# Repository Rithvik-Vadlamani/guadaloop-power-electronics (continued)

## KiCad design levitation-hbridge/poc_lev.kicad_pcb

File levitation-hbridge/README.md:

# poc_lev — levitation-coil H-bridge

KiCad 10 project for one nominal 60 V, bidirectional coil-driver channel. Built from the supplied brief, with the user's approved Bourns Kelvin pickup and revised component bands. No purchases or paid external services were used.

**Engineering review package. Hardware has not been built or powered.** The 30 A target, transient envelope and <5 nH commutation-loop target are not qualified. See the open release items in [DESIGN_NOTES.md](DESIGN_NOTES.md), especially the unknown charged-pack voltage, unmeasured coil, INA240 transient limit, heatsinks and requested human driver-pinout signoff.

The follow-up [hardware qualification review](HARDWARE_QUALIFICATION.md) includes conditional transient, ripple and thermal calculations. The user confirmed that no assembled board exists; physical qualification is blocked until hardware is available.

The approved [J3 edge-placement revision](INTERFACE_REVIEW.md) is applied: the header, control buffer, input resistors and auxiliary rail-entry components are regrouped near the bottom edge.

## Open and review

Open `poc_lev.kicad_pro` with KiCad 10.0.3 or later. The schematic is one flat sheet; the PCB is a routed four-layer, 146 × 96 mm board. Standard KiCad symbol/footprint libraries are required. Project-specific libraries are included and use `${KIPRJMOD}` paths.

- `poc_lev.kicad_sch` — editable schematic; exact 34-net specification.
- `poc_lev.kicad_pcb` — editable board, filled copper and four mounting holes.
- `poc_lev.kicad_pro`, `poc_lev.kicad_dru` — project settings and layout rules.
- `poc_lev.kicad_sym`, `lib.pretty/`, library tables — local symbols and footprints.
- `BOM.csv` — 64 electrical parts plus six test points and four mounting holes, including required component ratings.
- `VERIFICATION.md`, `reports/verification.json` — measured results and method.
- `DESIGN_NOTES.md` — source corrections, calculations, stackup and release items.
- `BRING_UP.md` — control pinout, current sign, logic states and required bench-test ladder.
- `reports/schematic-preview.png`, `reports/pcb-preview.png` — review images; native files remain authoritative.
- `sources/` — supplied brief and source documents/figures used during the review.

No fabrication order has been placed. No Gerber set is represented as approved for fabrication.

## Validation

On this Mac, run `zsh scripts/check.sh`. This invokes native KiCad ERC, native DRC and an independent parser that reconstructs schematic connectivity from wire/pin/label geometry, cross-checks the native XML netlist and checks the PCB pad mappings. Gate-loop measurements include component pad spans and the explicit source-return traces; via traversal contributes the nominal 1.6 mm board thickness. Parallel copper-plane returns are not assigned an invented length or inductance.

The matching requirement is checked within each half-bridge. The two shunt-to-filter copper paths are explicitly length matched. Decoupling distances are pad-center placement measurements; they are not field-extracted inductance values. Native DRC enforces 0.25 mm courtyard clearance and prohibits inner-layer tracks.

## Rebuild sources

The native files are ready to open without Python. Scripts are also supplied for reproducibility. `scripts/rebuild.sh` **overwrites the generated schematic and PCB**, so save any manual edits elsewhere first and close KiCad.

The build uses free, local software: KiCad 10.0.3, its bundled Python 3.9/pcbnew/wx, and NumPy, SciPy and Shapely in `.venv`. The virtual environment itself is not part of the delivery archive. On the build machine it was created with:

```sh
/Applications/KiCad/KiCad.app/Contents/Frameworks/Python.framework/Versions/3.9/bin/python3 -m venv .venv
.venv/bin/python -m pip install -r scripts/requirements.txt
zsh scripts/rebuild.sh
```

`KICAD_CLI`, `KICAD_PYTHON` and `KICAD_SITE_PACKAGES` can override the macOS tool locations. The source scripts also contain the installed standard-library location; adapt it if building on another operating system. No cloud autorouter or account is needed.

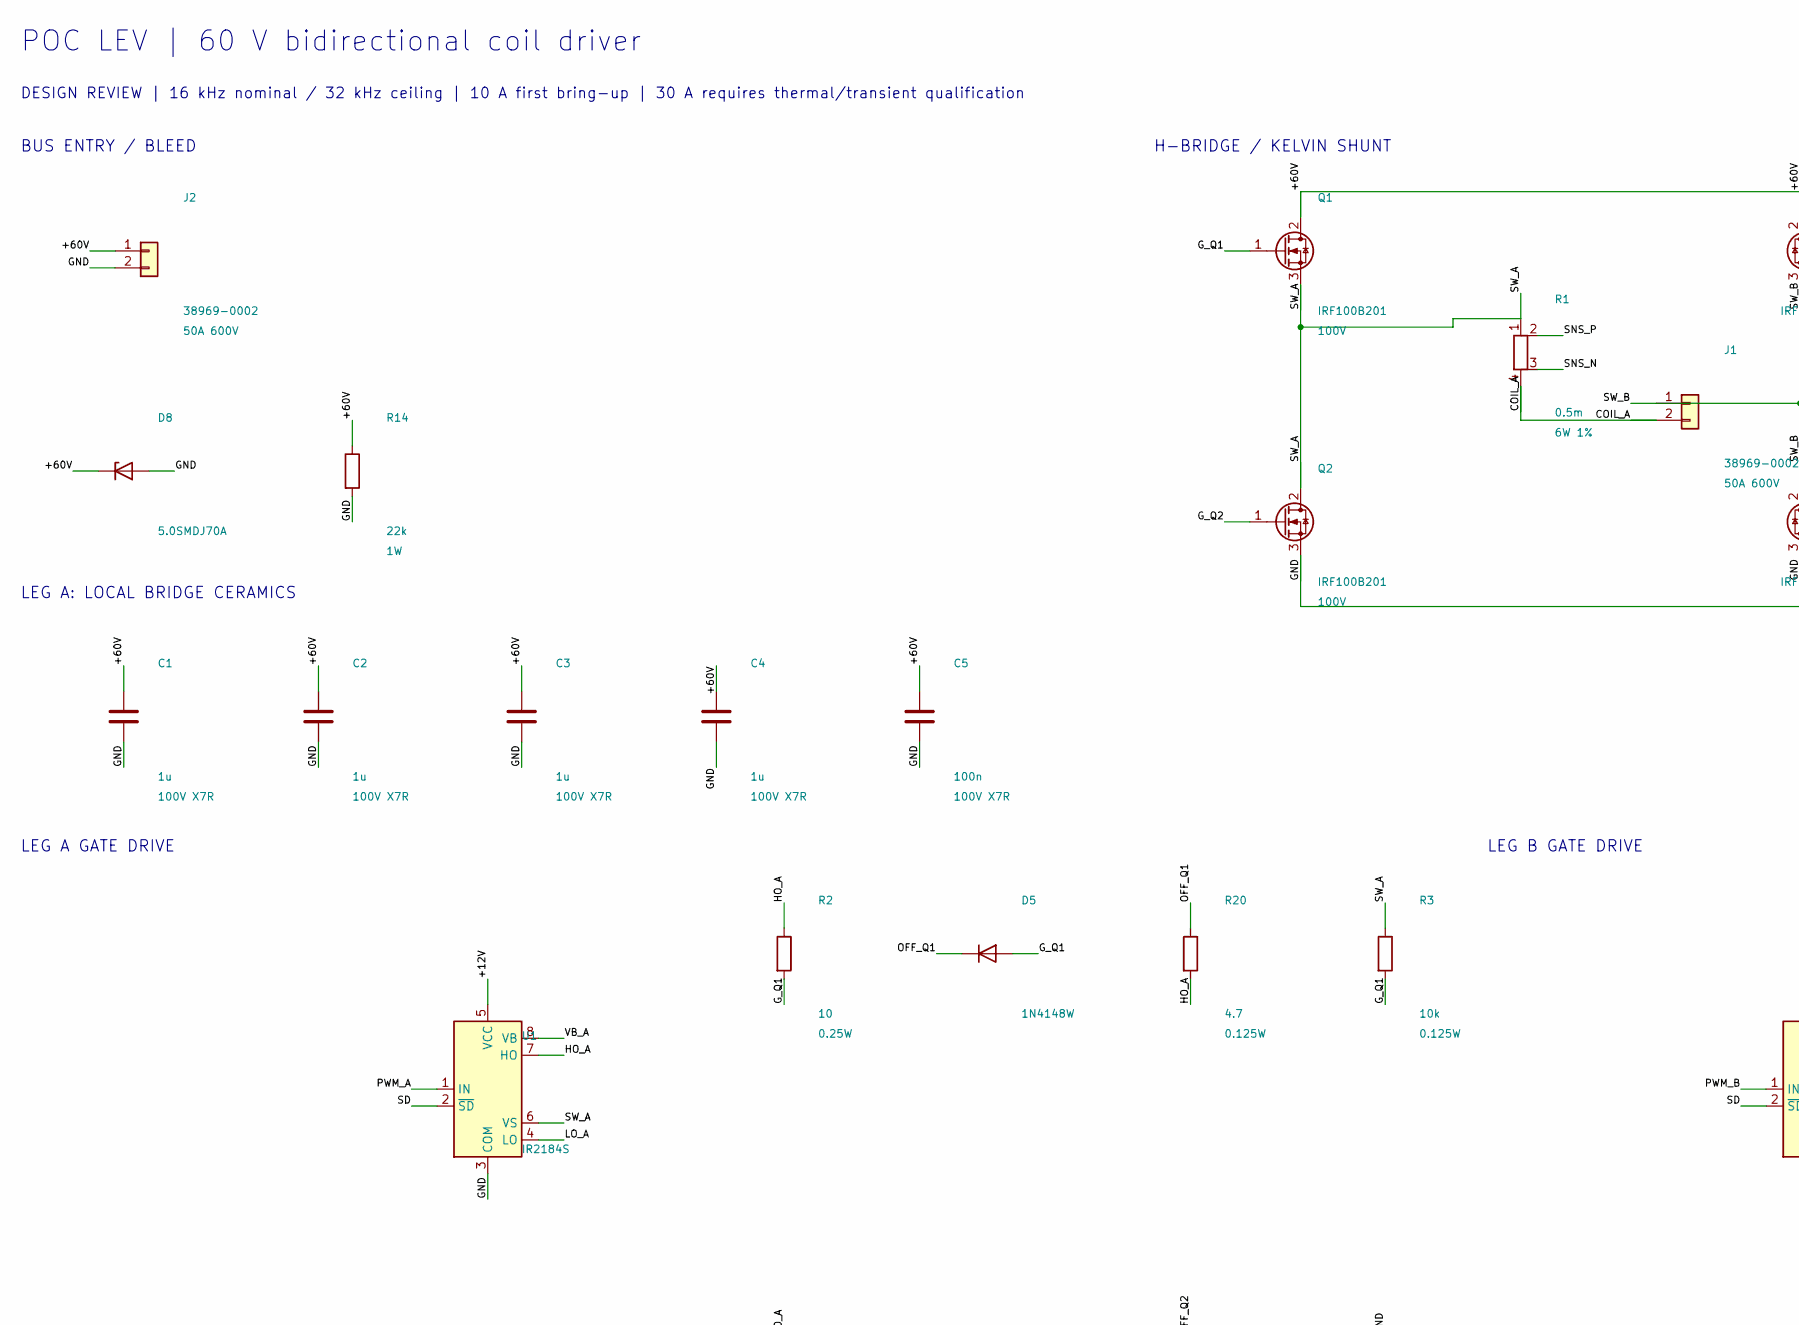
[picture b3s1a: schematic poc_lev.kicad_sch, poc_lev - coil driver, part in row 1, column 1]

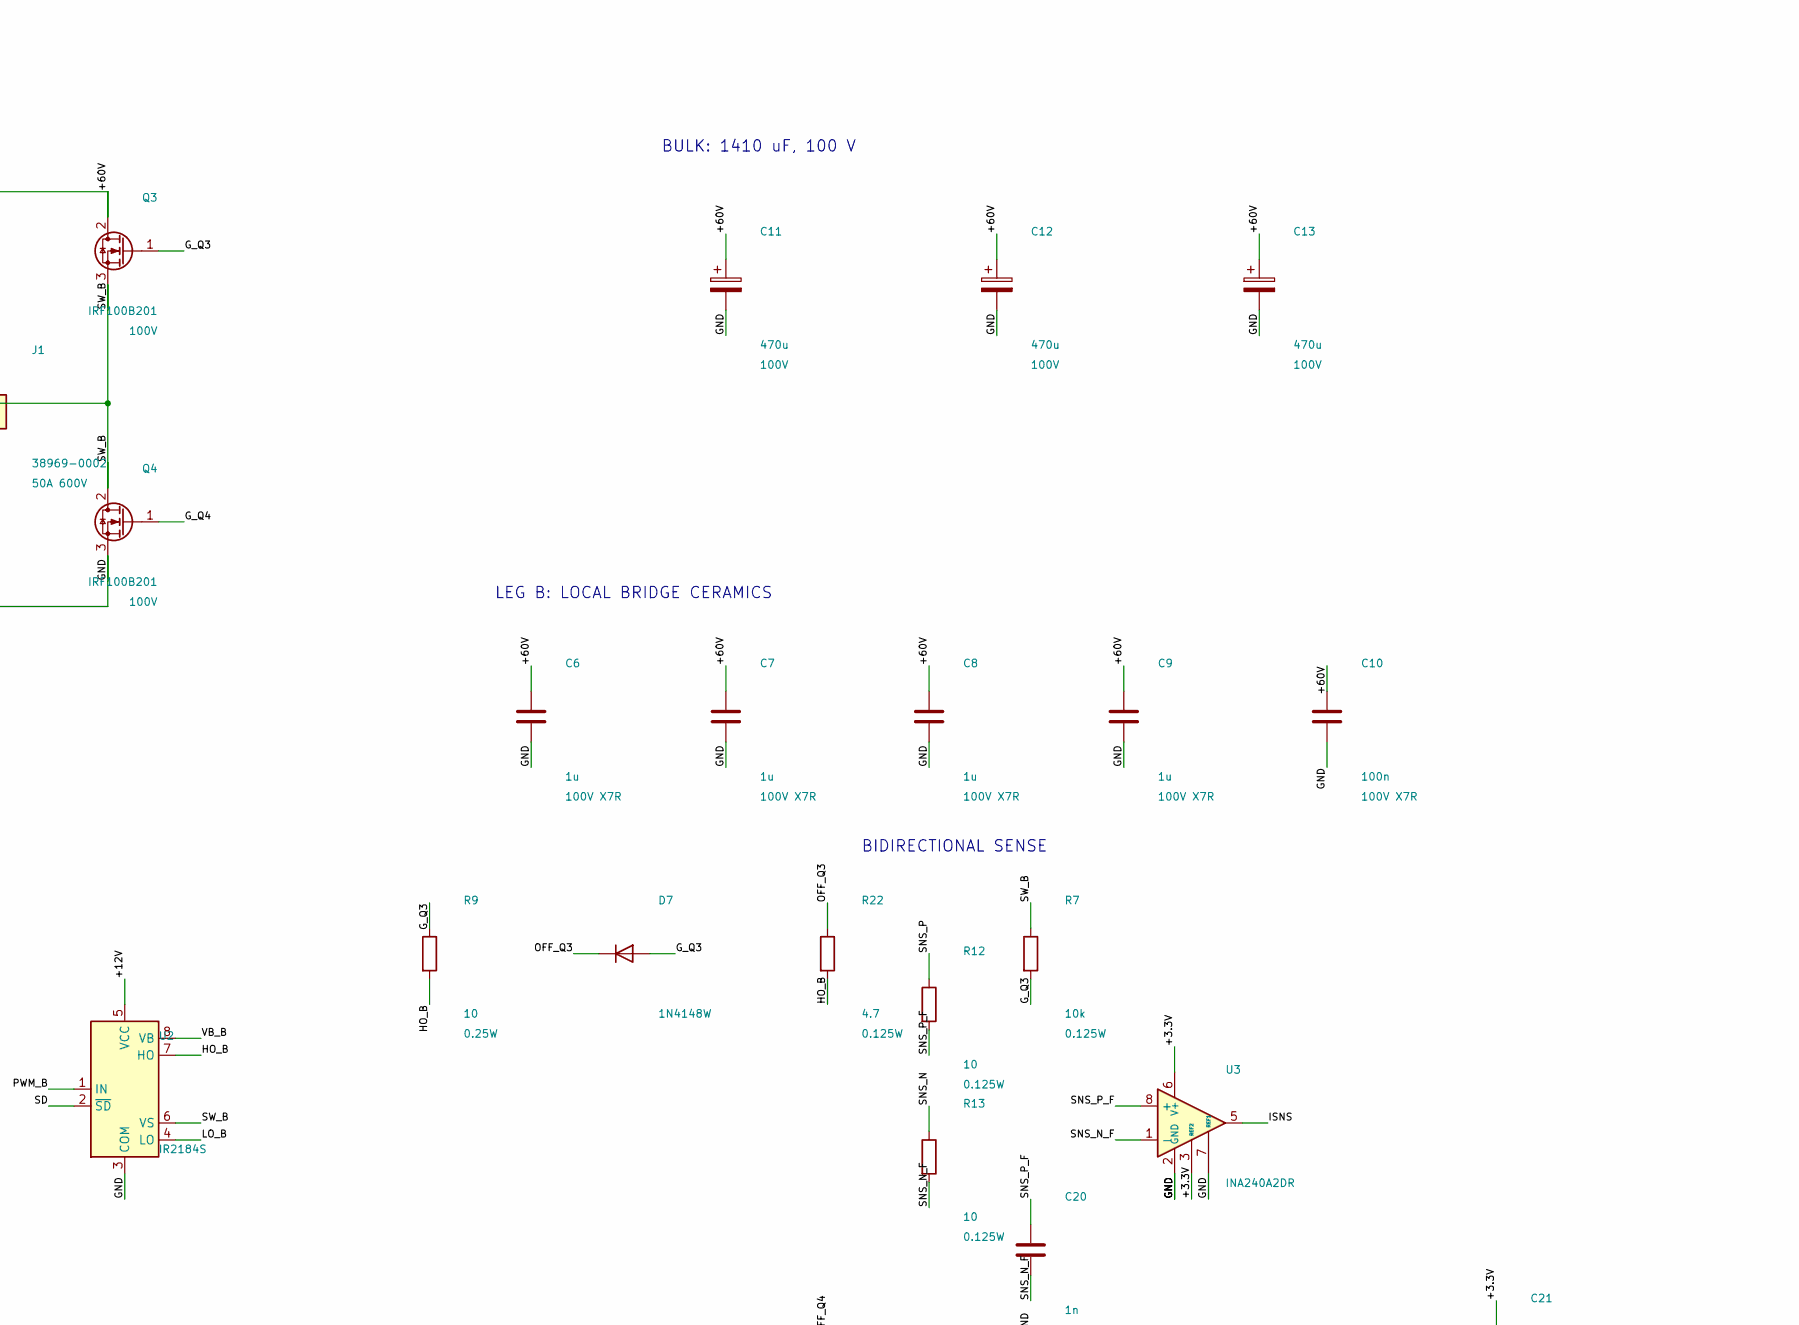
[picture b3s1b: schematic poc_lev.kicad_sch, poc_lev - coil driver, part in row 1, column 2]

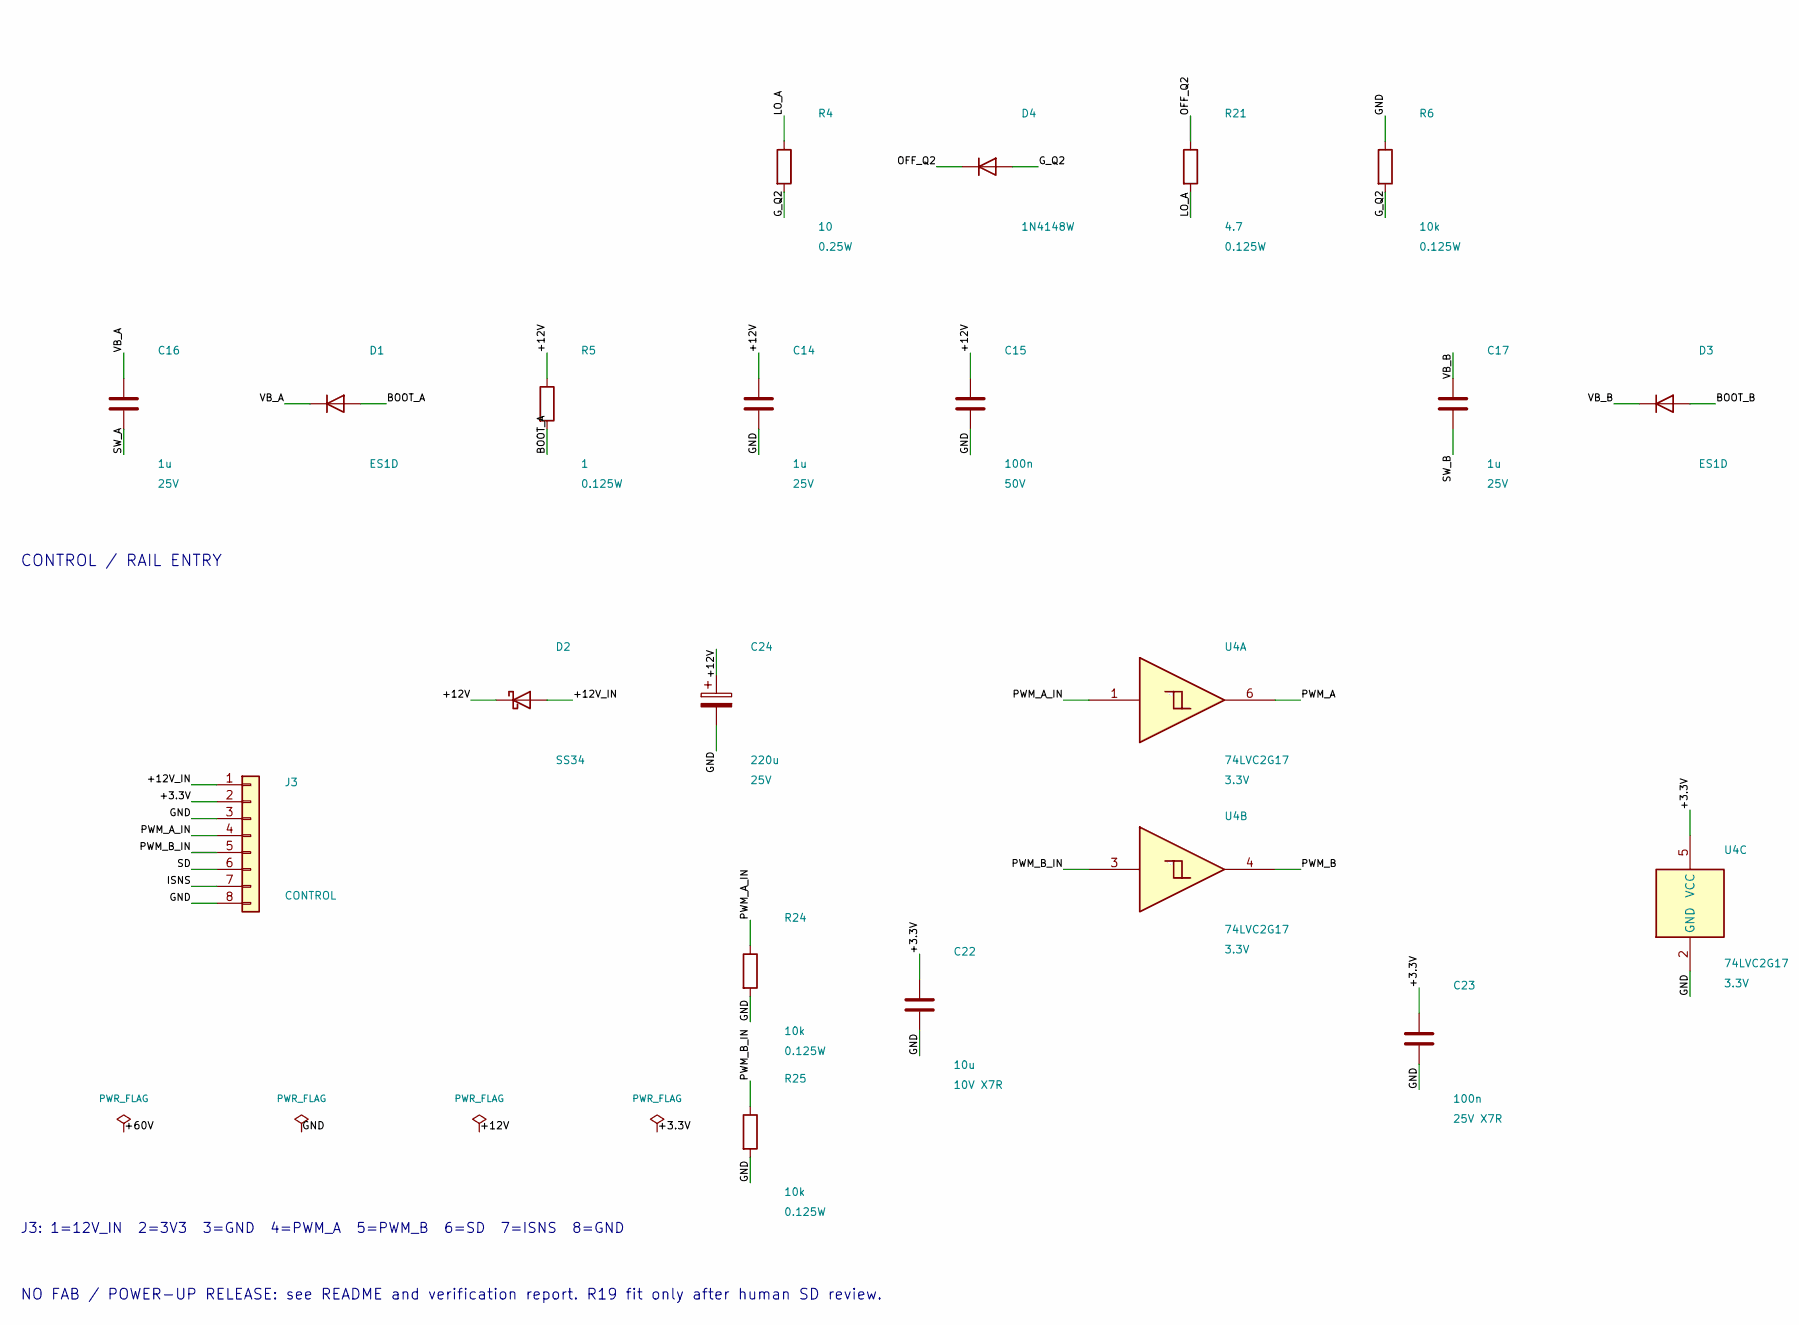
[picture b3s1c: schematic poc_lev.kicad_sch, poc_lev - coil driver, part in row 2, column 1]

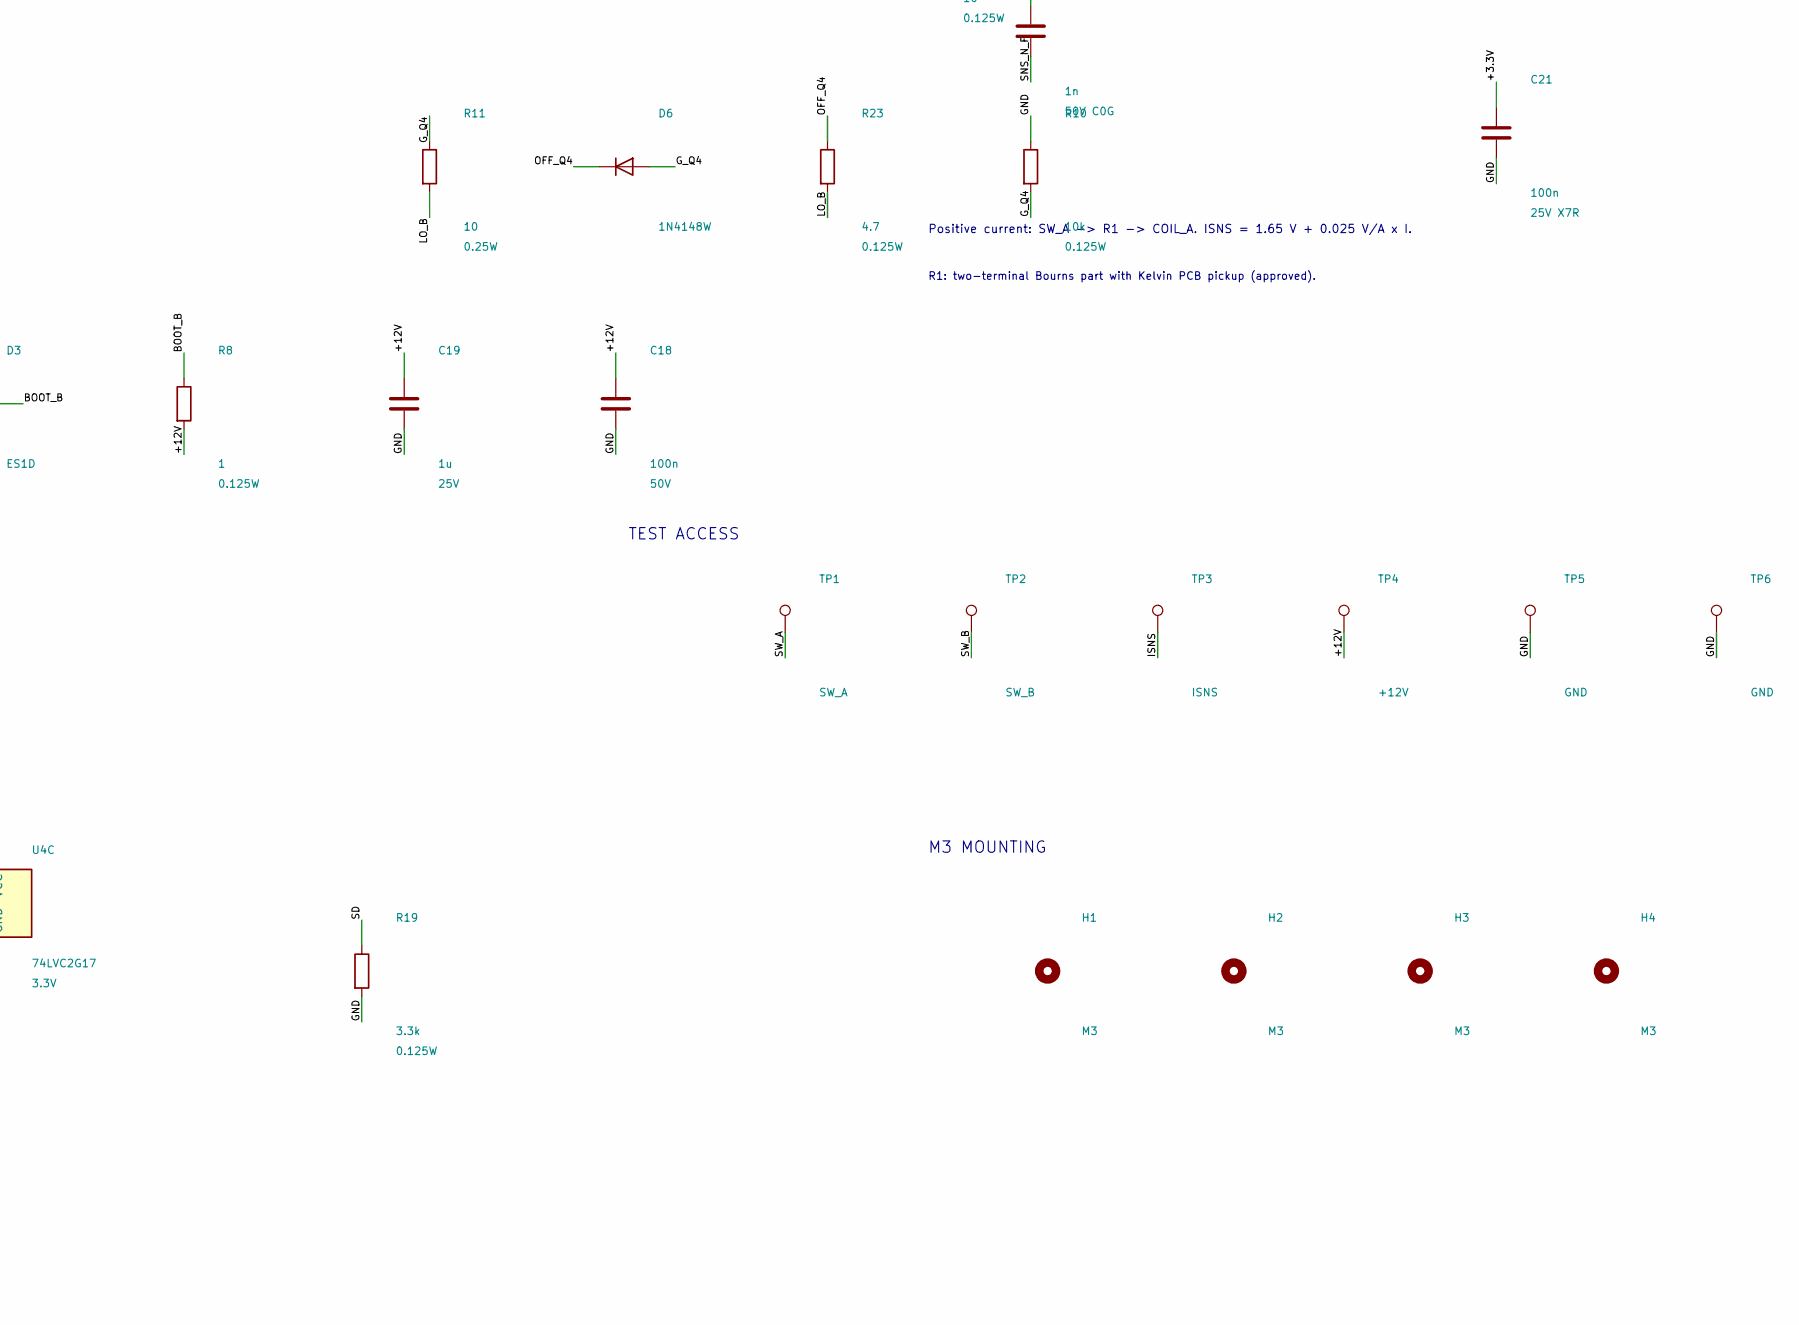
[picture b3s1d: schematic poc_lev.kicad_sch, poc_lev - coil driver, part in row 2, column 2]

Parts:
C1, C2, C3, C4, C6, C7, C8, C9: 1u; C_1210_3225Metric; Rating 100V X7R
C5, C10: 100n; C_0805_2012Metric; Rating 100V X7R
C11, C12, C13: 470u; CP_Radial_D16.0mm_P7.50mm; Rating 100V; MPN 100ZLH470MEFC16X31.5
C14, C16, C17, C19: 1u; C_0805_2012Metric; Rating 25V
C15, C18: 100n; C_0805_2012Metric; Rating 50V
C20: 1n; C_0805_2012Metric; Rating 50V C0G
C21, C23: 100n; C_0805_2012Metric; Rating 25V X7R
C22: 10u; C_0805_2012Metric; Rating 10V X7R
C24: 220u; CP_Radial_D8.0mm_P3.50mm_Positive2; Rating 25V
D1, D3: ES1D; D_SMA; MPN ES1D
D2: SS34; D_SMA; MPN SS34
D4, D5, D6, D7: 1N4148W; D_SOD-123; MPN 1N4148W
D8: 5.0SMDJ70A; D_SMC; MPN 5.0SMDJ70A
H1, H2, H3, H4: M3; MountingHole_3.2mm_M3
J1, J2: 38969-0002; CONN_SD-38969-001_02P_MOL; Rating 50A 600V; MPN 38969-0002
J3: CONTROL; PinHeader_1x08_P2.54mm_Vertical
Q1, Q2, Q3, Q4: IRF100B201; TO-220-3_Vertical; Rating 100V; MPN IRF100B201
R1: 0.5m; CSS2H_2512_Kelvin; Rating 6W 1%; MPN CSS2H-2512R-L500FE
R2, R4, R9, R11: 10; R_1206_3216Metric; Rating 0.25W
R3, R6, R7, R10, R24, R25: 10k; R_0805_2012Metric; Rating 0.125W
R5, R8: 1; R_0805_2012Metric; Rating 0.125W
R12, R13: 10; R_0805_2012Metric; Rating 0.125W
R14: 22k; R_2512_6332Metric; Rating 1W
R19: 3.3k; R_0805_2012Metric; Rating 0.125W
R20, R21, R22, R23: 4.7; R_0805_2012Metric; Rating 0.125W
TP1: SW_A; TestPoint_Pad_D2.0mm
TP2: SW_B; TestPoint_Pad_D2.0mm
TP3: ISNS; TestPoint_Pad_D2.0mm
TP4: +12V; TestPoint_Pad_D2.0mm
TP5, TP6: GND; TestPoint_Pad_D2.0mm
U1, U2: IR2184S; SOIC-8_3.9x4.9mm_P1.27mm; MPN IR2184SPBF
U3: INA240A2DR; SOIC-8_3.9x4.9mm_P1.27mm; MPN INA240A2DR
U4: 74LVC2G17; SOT-23-6; Rating 3.3V; MPN 74LVC2G17GV

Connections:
/+3.3V: C21.1, C22.1, C23.1, J3.2, U3.3 (REF2), U3.6 (V+), U4.5 (VCC)
/+12V: C14.1, C15.1, C18.1, C19.1, C24.2, D2.1 (K), R5.1, R8.2, TP4.1, U1.5 (VCC), U2.5 (VCC)
/+12V_IN: D2.2 (A), J3.1
/+60V: C1.1, C2.1, C3.1, C4.1, C5.1, C6.1, C7.1, C8.1, C9.1, C10.1, C11.1, C12.1, C13.1, D8.1 (K), J2.1, Q1.2 (D), Q3.2 (D), R14.1
/BOOT_A: D1.2 (A), R5.2
/BOOT_B: D3.2 (A), R8.1
/COIL_A: J1.2, R1.4
/GND: C1.2, C2.2, C3.2, C4.2, C5.2, C6.2, C7.2, C8.2, C9.2, C10.2, C11.2, C12.2, C13.2, C14.2, C15.2, C18.2, C19.2, C21.2, C22.2, C23.2, C24.1, D8.2 (A), J2.2, J3.3, J3.8, Q2.3 (S), Q4.3 (S), R6.1, R10.1, R14.2, R19.2, R24.2, R25.2, TP5.1, TP6.1, U1.3 (COM), U2.3 (COM), U3.2 (GND), U3.4 (GND), U3.7 (REF1), U4.2 (GND)
/G_Q1: D5.2 (A), Q1.1 (G), R2.2, R3.2
/G_Q2: D4.2 (A), Q2.1 (G), R4.2, R6.2
/G_Q3: D7.2 (A), Q3.1 (G), R7.2, R9.1
/G_Q4: D6.2 (A), Q4.1 (G), R10.2, R11.1
/HO_A: R2.1, R20.2, U1.7 (HO)
/HO_B: R9.2, R22.2, U2.7 (HO)
/ISNS: J3.7, TP3.1, U3.5
/LO_A: R4.1, R21.2, U1.4 (LO)
/LO_B: R11.2, R23.2, U2.4 (LO)
/OFF_Q1: D5.1 (K), R20.1
/OFF_Q2: D4.1 (K), R21.1
/OFF_Q3: D7.1 (K), R22.1
/OFF_Q4: D6.1 (K), R23.1
/PWM_A: U1.1 (IN), U4.6
/PWM_A_IN: J3.4, R24.1, U4.1
/PWM_B: U2.1 (IN), U4.4
/PWM_B_IN: J3.5, R25.1, U4.3
/SD: J3.6, R19.1, U1.2 (~SD), U2.2 (~SD)
/SNS_N: R1.3, R13.1
/SNS_N_F: C20.2, R13.2, U3.1 (-)
/SNS_P: R1.2, R12.1
/SNS_P_F: C20.1, R12.2, U3.8 (+)
/SW_A: C16.2, Q1.3 (S), Q2.2 (D), R1.1, R3.1, TP1.1, U1.6 (VS)
/SW_B: C17.2, J1.1, Q3.3 (S), Q4.2 (D), R7.1, TP2.1, U2.6 (VS)
/VB_A: C16.1, D1.1 (K), U1.8 (VB)
/VB_B: C17.1, D3.1 (K), U2.8 (VB)

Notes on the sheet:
POC LEV | 60 V bidirectional coil driver
DESIGN REVIEW | 16 kHz nominal / 32 kHz ceiling | 10 A first bring-up | 30 A requires thermal/transient qualification
BUS ENTRY / BLEED
H-BRIDGE / KELVIN SHUNT
BULK: 1410 uF, 100 V
LEG A: LOCAL BRIDGE CERAMICS
LEG B: LOCAL BRIDGE CERAMICS
LEG A GATE DRIVE
LEG B GATE DRIVE
BIDIRECTIONAL SENSE
CONTROL / RAIL ENTRY
TEST ACCESS
M3 MOUNTING
Positive current: SW_A -> R1 -> COIL_A. ISNS = 1.65 V + 0.025 V/A x I.
R1: two-terminal Bourns part with Kelvin PCB pickup (approved).
NO FAB / POWER-UP RELEASE: see README and verification report. R19 fit only after human SD review.
J3: 1=12V_IN 2=3V3 3=GND 4=PWM_A 5=PWM_B 6=SD 7=ISNS 8=GND

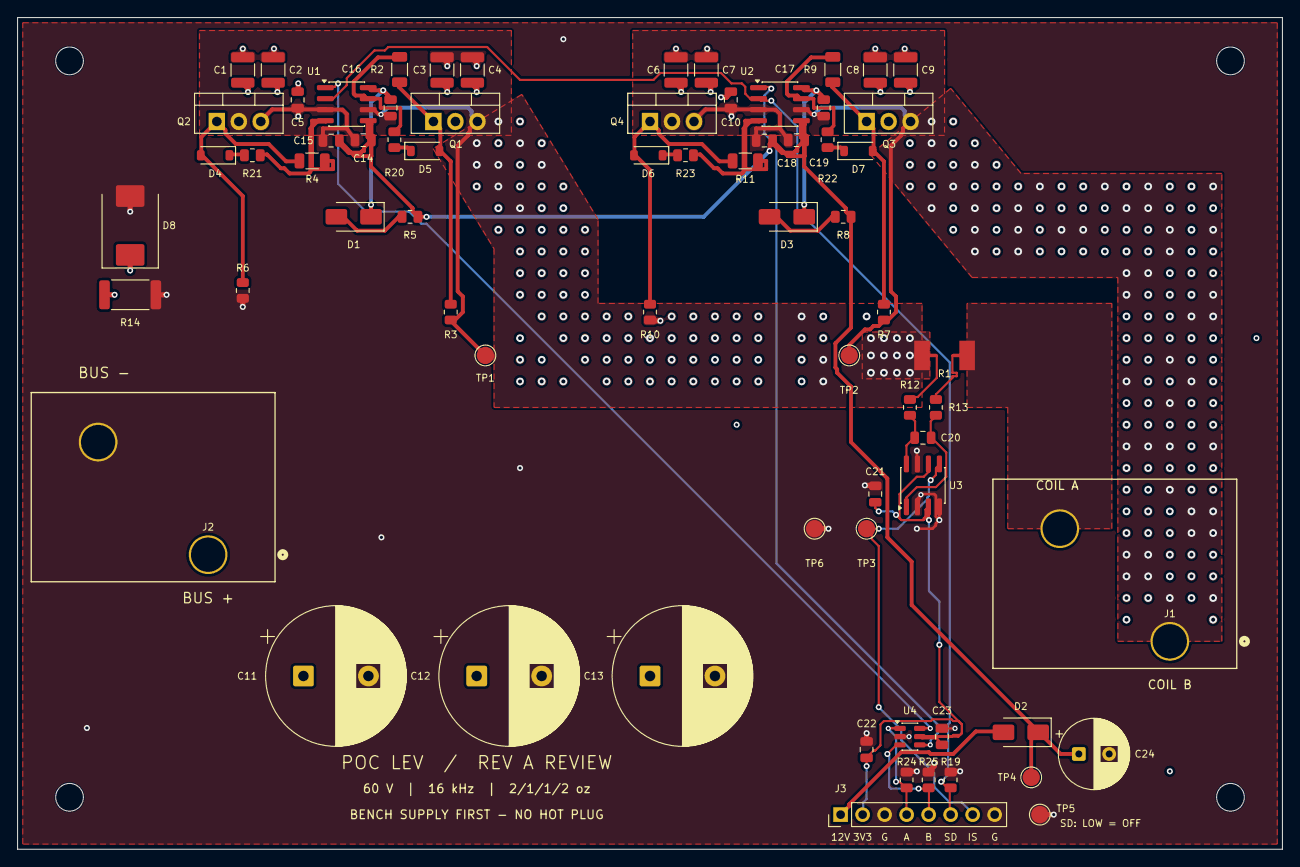
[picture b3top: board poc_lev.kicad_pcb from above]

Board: 4 copper layers, 146.0 x 96.0 mm, 74 parts (0 on the bottom side), 34 nets.

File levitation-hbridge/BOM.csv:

ref,value,mpn,rating,footprint,note
Q1,IRF100B201,IRF100B201,100V,Package_TO_SOT_THT:TO-220-3_Vertical,Individual insulated clip-on heatsink; 30A thermal design unqualified
Q2,IRF100B201,IRF100B201,100V,Package_TO_SOT_THT:TO-220-3_Vertical,Individual insulated clip-on heatsink; 30A thermal design unqualified
Q3,IRF100B201,IRF100B201,100V,Package_TO_SOT_THT:TO-220-3_Vertical,Individual insulated clip-on heatsink; 30A thermal design unqualified
Q4,IRF100B201,IRF100B201,100V,Package_TO_SOT_THT:TO-220-3_Vertical,Individual insulated clip-on heatsink; 30A thermal design unqualified
C1,1u,,100V X7R,Capacitor_SMD:C_1210_3225Metric,
C2,1u,,100V X7R,Capacitor_SMD:C_1210_3225Metric,
C3,1u,,100V X7R,Capacitor_SMD:C_1210_3225Metric,
C4,1u,,100V X7R,Capacitor_SMD:C_1210_3225Metric,
C5,100n,,100V X7R,Capacitor_SMD:C_0805_2012Metric,
C6,1u,,100V X7R,Capacitor_SMD:C_1210_3225Metric,
C7,1u,,100V X7R,Capacitor_SMD:C_1210_3225Metric,
C8,1u,,100V X7R,Capacitor_SMD:C_1210_3225Metric,
C9,1u,,100V X7R,Capacitor_SMD:C_1210_3225Metric,
C10,100n,,100V X7R,Capacitor_SMD:C_0805_2012Metric,
C11,470u,100ZLH470MEFC16X31.5,100V,Capacitor_THT:CP_Radial_D16.0mm_P7.50mm,
C12,470u,100ZLH470MEFC16X31.5,100V,Capacitor_THT:CP_Radial_D16.0mm_P7.50mm,
C13,470u,100ZLH470MEFC16X31.5,100V,Capacitor_THT:CP_Radial_D16.0mm_P7.50mm,
C14,1u,,25V,Capacitor_SMD:C_0805_2012Metric,
C15,100n,,50V,Capacitor_SMD:C_0805_2012Metric,
C16,1u,,25V,Capacitor_SMD:C_0805_2012Metric,
C17,1u,,25V,Capacitor_SMD:C_0805_2012Metric,
C18,100n,,50V,Capacitor_SMD:C_0805_2012Metric,
C19,1u,,25V,Capacitor_SMD:C_0805_2012Metric,
C20,1n,,50V C0G,Capacitor_SMD:C_0805_2012Metric,
C21,100n,,25V X7R,Capacitor_SMD:C_0805_2012Metric,
C22,10u,,10V X7R,Capacitor_SMD:C_0805_2012Metric,
C23,100n,,25V X7R,Capacitor_SMD:C_0805_2012Metric,
C24,220u,,25V,poc_lev:CP_Radial_D8.0mm_P3.50mm_Positive2,C24 positive pad 2 preserves source netlist
R1,0.5m,CSS2H-2512R-L500FE,6W 1%,poc_lev:CSS2H_2512_Kelvin,Two-terminal component with manufacturer-recommended Kelvin PCB pickup; user accepted
R2,10,,0.25W; pulse capability to verify,Resistor_SMD:R_1206_3216Metric,
R3,10k,,0.125W,Resistor_SMD:R_0805_2012Metric,
R4,10,,0.25W; pulse capability to verify,Resistor_SMD:R_1206_3216Metric,
R5,1,,0.125W,Resistor_SMD:R_0805_2012Metric,
R6,10k,,0.125W,Resistor_SMD:R_0805_2012Metric,
R7,10k,,0.125W,Resistor_SMD:R_0805_2012Metric,
R8,1,,0.125W,Resistor_SMD:R_0805_2012Metric,
R9,10,,0.25W; pulse capability to verify,Resistor_SMD:R_1206_3216Metric,
R10,10k,,0.125W,Resistor_SMD:R_0805_2012Metric,
R11,10,,0.25W; pulse capability to verify,Resistor_SMD:R_1206_3216Metric,
R12,10,,0.125W,Resistor_SMD:R_0805_2012Metric,
R13,10,,0.125W,Resistor_SMD:R_0805_2012Metric,
R14,22k,,1W,Resistor_SMD:R_2512_6332Metric,
R19,3.3k,,0.125W,Resistor_SMD:R_0805_2012Metric,
R20,4.7,,0.125W,Resistor_SMD:R_0805_2012Metric,
R21,4.7,,0.125W,Resistor_SMD:R_0805_2012Metric,
R22,4.7,,0.125W,Resistor_SMD:R_0805_2012Metric,
R23,4.7,,0.125W,Resistor_SMD:R_0805_2012Metric,
R24,10k,,0.125W,Resistor_SMD:R_0805_2012Metric,
R25,10k,,0.125W,Resistor_SMD:R_0805_2012Metric,
D1,ES1D,ES1D,,Diode_SMD:D_SMA,
D2,SS34,SS34,,Diode_SMD:D_SMA,
D3,ES1D,ES1D,,Diode_SMD:D_SMA,
D4,1N4148W,1N4148W,,Diode_SMD:D_SOD-123,
D5,1N4148W,1N4148W,,Diode_SMD:D_SOD-123,
D6,1N4148W,1N4148W,,Diode_SMD:D_SOD-123,
D7,1N4148W,1N4148W,,Diode_SMD:D_SOD-123,
D8,5.0SMDJ70A,5.0SMDJ70A,,Diode_SMD:D_SMC,
U1,IR2184S,IR2184SPBF,,Package_SO:SOIC-8_3.9x4.9mm_P1.27mm,SOIC-8 ordering code; pinout human review required by brief
U2,IR2184S,IR2184SPBF,,Package_SO:SOIC-8_3.9x4.9mm_P1.27mm,SOIC-8 ordering code; pinout human review required by brief
U3,INA240A2DR,INA240A2DR,,Package_SO:SOIC-8_3.9x4.9mm_P1.27mm,
U4,74LVC2G17,74LVC2G17GV,3.3V,Package_TO_SOT_SMD:SOT-23-6,
J1,38969-0002,38969-0002,50A 600V,poc_lev:CONN_SD-38969-001_02P_MOL,
J2,38969-0002,38969-0002,50A 600V,poc_lev:CONN_SD-38969-001_02P_MOL,
J3,CONTROL,,,Connector_PinHeader_2.54mm:PinHeader_1x08_P2.54mm_Vertical,
H1,M3,,,MountingHole:MountingHole_3.2mm_M3,
H2,M3,,,MountingHole:MountingHole_3.2mm_M3,
H3,M3,,,MountingHole:MountingHole_3.2mm_M3,
H4,M3,,,MountingHole:MountingHole_3.2mm_M3,
TP1,SW_A,,,TestPoint:TestPoint_Pad_D2.0mm,
TP2,SW_B,,,TestPoint:TestPoint_Pad_D2.0mm,
TP3,ISNS,,,TestPoint:TestPoint_Pad_D2.0mm,
TP4,+12V,,,TestPoint:TestPoint_Pad_D2.0mm,
TP5,GND,,,TestPoint:TestPoint_Pad_D2.0mm,
TP6,GND,,,TestPoint:TestPoint_Pad_D2.0mm,

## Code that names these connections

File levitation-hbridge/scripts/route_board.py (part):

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    loc('GND',[(50,30.8),(47.25,30.8),(47.25,32.2)])
    loc('+12V',[(52.475,29.905),(52.85,30.28),(52.85,32.15)])
    loc('+12V',[(52.85,32.15),(52.85,34),(50.9,34),(49.15,32.2)])
    loc('HO_A' if u==1 else 'HO_B',[(52.475,27.365),(53.89,27.365),(53.89,28.43),(56.2,28.43),(56.2,30.4875),(55.5,31.1875)],.4)
    sn='SW_A' if u==1 else 'SW_B'
    loc(sn,[(52.475,28.635),(53.145,28.635),(53.69,29.18),(53.95,29.18),(54.85,29.18),(55.05,29.38)],.4)
    addvia(sn,(53.95+off,29.18),.6,.3)
    pts=[(65.08,30),(64.4,29.32),(64.4,28.8),(64,28.4),(54.73,28.4),(53.95,29.18)]
    for a,c in zip(pts,pts[1:]):addtrack(sn,1,(a[0]+off,a[1]),(c[0]+off,c[1]),.45)
    loc('LO_A' if u==1 else 'LO_B',[(47.525,29.905),(46,29.905),(46,35.5),(48.4125,35.5),(48.4125,34.55),(47.4625,34.55)])
# Gate landing and off paths are routed around the explicit driver routes.
for n in GATE:
    keys=[k for k in NETS[n] if k not in ['R3.2','R6.2','R7.2','R10.2']]
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    elif n.startswith('LO_'):route(n,xy(P[keys[0]].GetPosition()),xy(P[keys[-1]].GetPosition()),.45,False)
    else:routepins(n,keys,.45,False)
# Bootstrap and supply caps local to each driver.
for n in ['VB_A','VB_B','BOOT_A','BOOT_B']:routepins(n,NETS[n],.45,True)
# Kelvin pair starts at inner shunt land edges, not force pad centers.
for n in ['SNS_P','SNS_N','SNS_P_F','SNS_N_F']:routepins(n,NETS[n],.25,False)
# Remaining gate pulldown branches, far from switching paths.
for n,k in [('G_Q1','R3.2'),('G_Q2','R6.2'),('G_Q3','R7.2'),('G_Q4','R10.2')]:
    nearest=min((z for z in NETS[n] if z!=k),key=lambda z:math.dist(xy(P[z].GetPosition()),xy(P[k].GetPosition())))
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addtrack('GND',0,xy(P['C23.2'].GetPosition()),(120.2,100.05),.25);addvia('GND',(120.2,100.05),.6,.3)
manual('+3.3V',[(116.1375,101),(118,101),(118.7,101.95)],.25)
# Establish off-pad escapes for the compact buffer before long supply/control routing.
for net,pin,end in [('PWM_A_IN','U4.1',(112.5,100.05)),('PWM_B_IN','U4.3',(112.5,101.95)),('PWM_B','U4.4',(117.35,101.95)),('PWM_A','U4.6',(117.35,100.05))]:
    addtrack(net,0,xy(P[pin].GetPosition()),end,.25);addvia(net,end,.6,.3)
for n in ['SD','+12V','+12V_IN','+3.3V','PWM_A_IN','PWM_B_IN','PWM_A','PWM_B','ISNS']:
    routepins(n,NETS[n],.45 if n.startswith('+12') else .25,True)
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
